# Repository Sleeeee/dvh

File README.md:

# dvh
Damn Vulnerable Hardware (DVH)

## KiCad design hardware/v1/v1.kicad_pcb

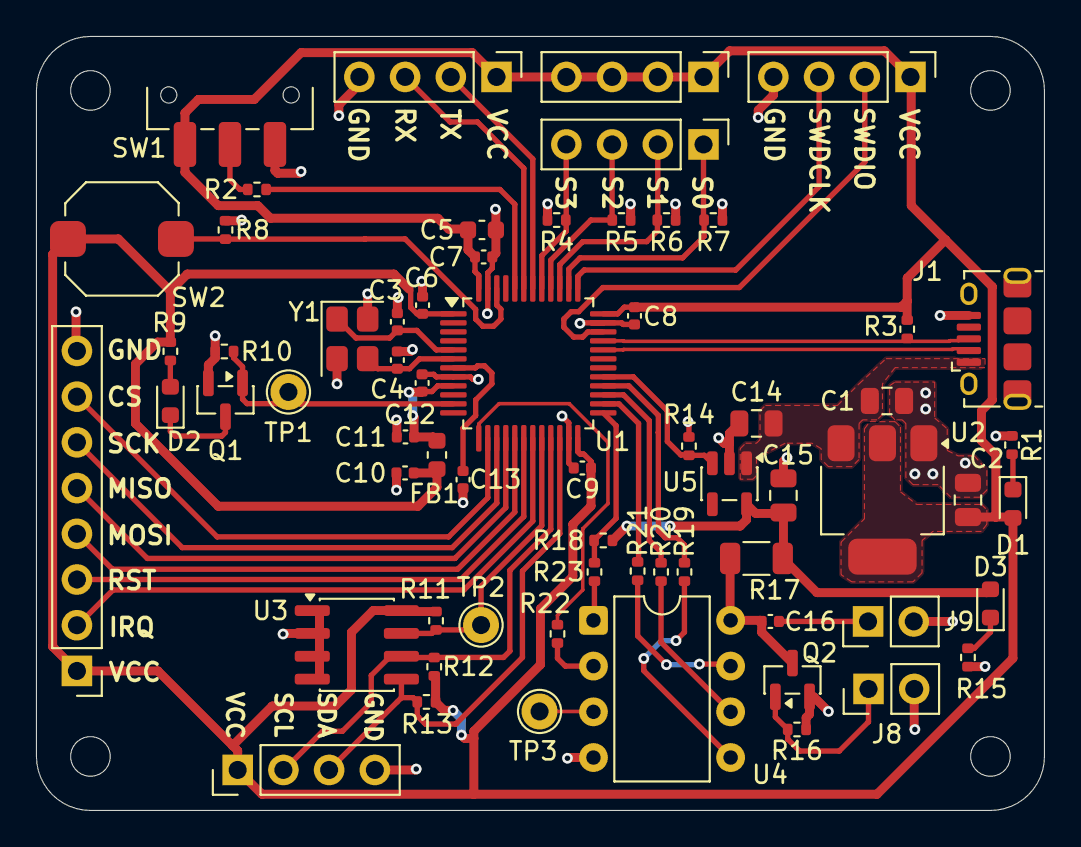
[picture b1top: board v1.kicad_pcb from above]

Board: 2 copper layers, 56.0 x 43.0 mm, 69 parts (0 on the bottom side), 50 nets.

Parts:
C1, C2: 22u; C_0805_2012Metric
C3, C4: 10p; C_0402_1005Metric
C5: 10u; C_0603_1608Metric
C6, C7, C8, C9, C13, C16: 100n; C_0402_1005Metric
C10, C11: 1u; C_0402_1005Metric
C12: 10n; C_0402_1005Metric
C14, C15: 1u; C_0805_2012Metric
D1, D3: RED; LED_0603_1608Metric
D2: GREEN; LED_0603_1608Metric
FB1: 120R; L_0603_1608Metric
H1, H2, H3, H4: MountingHole; MountingHole_2.2mm_M2
J1: USB_B_Micro; USB_Micro-B_Amphenol_10118194-0001LF_Horizontal
J2: SEL_IN; PinHeader_1x04_P2.54mm_Vertical
J3: SEL_VDD; PinHeader_1x04_P2.54mm_Vertical
J4: SWD_INT; PinHeader_1x04_P2.54mm_Vertical
J5: UART_INT; PinHeader_1x04_P2.54mm_Vertical
J6: I2C_INT; PinHeader_1x04_P2.54mm_Vertical
J7: RFID_INT; PinHeader_1x08_P2.54mm_Vertical
J8: GLITCH_IN; PinHeader_1x02_P2.54mm_Vertical
J9: GLITCH_EN; PinHeader_1x02_P2.54mm_Vertical
Q1, Q2: 2N7002; SOT-23
R1, R3, R9, R12, R13, R15, R19, R20, R21, R22, R23: 1k5; R_0402_1005Metric
R2, R4, R5, R6, R7, R8, R10, R11, R14, R16, R18: 10k; R_0402_1005Metric
R17: 47; R_1206_3216Metric
SW1: SW_BOOT0; SW_SPDT_CK_JS102011SAQN
SW2: LAB_RST; SW_Push_1TS009xxxx-xxxx-xxxx_6x6x5mm
TP1: DOOR; TestPoint_THTPad_D2.0mm_Drill1.0mm
TP2: WP; TestPoint_THTPad_D2.0mm_Drill1.0mm
TP3: GLITCH_TRIG; TestPoint_THTPad_D2.0mm_Drill1.0mm
U1: STM32F103C8Tx; LQFP-48_7x7mm_P0.5mm
U2: AMS1117-3.3; SOT-223-3_TabPin2
U3: M24C02-WMN; SOIC-8_3.9x4.9mm_P1.27mm
U4: ATtiny85-20P; DIP-8_W7.62mm
U5: AP2112K-3.3; SOT-23-5
Y1: 16MHz; Crystal_SMD_3225-4Pin_3.2x2.5mm

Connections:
+3.3V: C2.1, C5.1, C6.1, C7.1, C8.1, C9.1, C10.1, D1.2 (A), FB1.1, J3.1, J3.2, J3.3, J3.4, J4.1, J5.1, J6.1, J7.1, R3.1, R9.2, R11.1, R12.1, R13.1, SW1.3 (C), SW2.1, U1.1 (VBAT), U1.24 (VDD), U1.36 (VDD), U1.48 (VDD), U2.2 (VO), U3.8 (VCC)
+3.3VA: C11.1, C12.1, FB1.2, U1.9 (VDDA)
+3.3V_ATTINY: C15.1, D3.2 (A), R17.1, R18.2, U5.5 (VOUT)
/Base/PWR_LED_K: D1.1 (K), R1.1
/Base/SW_BOOT0: R2.1, SW1.2 (B)
/Connectivity/DOOR_LED_A: D2.2 (A), R9.1
/Connectivity/DOOR_LED_K: D2.1 (K), Q1.3 (D)
/Glitching/ATTINY_MISO: R20.1, U4.6 (PB1)
/Glitching/ATTINY_MOSI: R19.1, U4.5 (AREF/PB0)
/Glitching/ATTINY_RST: R23.1, U4.1 (~RESET/PB5)
/Glitching/ATTINY_SCK: R21.1, U4.7 (PB2)
/Glitching/ATTINY_TRIG: TP3.1, U4.3 (XTAL2/PB4)
/Glitching/ATTINY_TX: R22.1, U4.2 (XTAL1/PB3)
/Glitching/ATTINY_VCC: C16.2, Q2.3 (D), R17.2, U4.8 (VCC)
/Glitching/GLITCH_EN: C16.1, J9.1
/Glitching/GLITCH_IN: J8.1, Q2.1 (G), R16.2
/Glitching/PWR_LED_K: D3.1 (K), R15.1
BOOT0: R2.2, U1.44 (BOOT0)
DOOR_OUT: Q1.1 (G), R10.2, TP1.1, U1.11 (PA1)
EEPROM_WP: R11.2, TP2.1, U1.20 (PB2), U3.7 (~WC)
GLITCH_RST_OUT: R18.1, R23.2, U1.25 (PB12)
GND: C1.2, C2.2, C3.2, C4.2, C5.2, C6.2, C7.2, C8.2, C9.2, C10.2, C11.2, C12.2, C13.2, C14.2, C15.2, J1.5 (GND), J4.4, J5.4, J6.4, J7.8, J8.2, J9.2, Q1.2 (S), Q2.2 (S), R1.2, R4.2, R5.2, R6.2, R7.2, R8.2, R10.1, R14.1, R15.2, R16.1, SW1.1 (A), U1.8 (VSSA), U1.23 (VSS), U1.35 (VSS), U1.47 (VSS), U2.1 (GND), U3.1 (E0), U3.2 (E1), U3.3 (E2), U3.4 (VSS), U4.4 (GND), U5.2 (GND), Y1.2 (G), Y1.4 (G)
HSE_IN: C3.1, U1.5 (PD0), Y1.1
HSE_OUT: C4.1, U1.6 (PD1), Y1.3
I2C_SCL: J6.2, R12.2, U1.21 (PB10), U3.6 (SCL)
I2C_SDA: J6.3, R13.2, U1.22 (PB11), U3.5 (SDA)
LAB_RST: R8.1, SW2.2, U1.46 (PB9)
LAB_S0: J2.1, R7.1, U1.38 (PA15)
LAB_S1: J2.2, R6.1, U1.39 (PB3)
LAB_S2: J2.3, R5.1, U1.40 (PB4)
LAB_S3: J2.4, R4.1, U1.41 (PB5)
LDO_EN: R14.2, U1.29 (PA8), U5.3 (EN)
NRST: C13.1, U1.7 (NRST)
RFID_IRQ: J7.2, U1.19 (PB1)
RFID_RST: J7.3, U1.18 (PB0)
SPI1_CS: J7.7, U1.14 (PA4)
SPI1_MISO: J7.5, U1.16 (PA6)
SPI1_MOSI: J7.4, U1.17 (PA7)
SPI1_SCK: J7.6, U1.15 (PA5)
SPI2_MISO: R20.2, U1.27 (PB14)
SPI2_MOSI: R19.2, U1.28 (PB15)
SPI2_SCK: R21.2, U1.26 (PB13)
SWDCLK: J4.3, U1.37 (PA14)
SWDIO: J4.2, U1.34 (PA13)
UART1_RX: J5.3, U1.43 (PB7)
UART1_TX: J5.2, U1.42 (PB6)
UART2_RX: R22.2, U1.13 (PA3)
USB_D+: J1.3 (D+), R3.2, U1.33 (PA12)
USB_D-: J1.2 (D-), U1.32 (PA11)
VBUS: C1.1, C14.1, J1.1 (VBUS), U2.3 (VI), U5.1 (VIN)

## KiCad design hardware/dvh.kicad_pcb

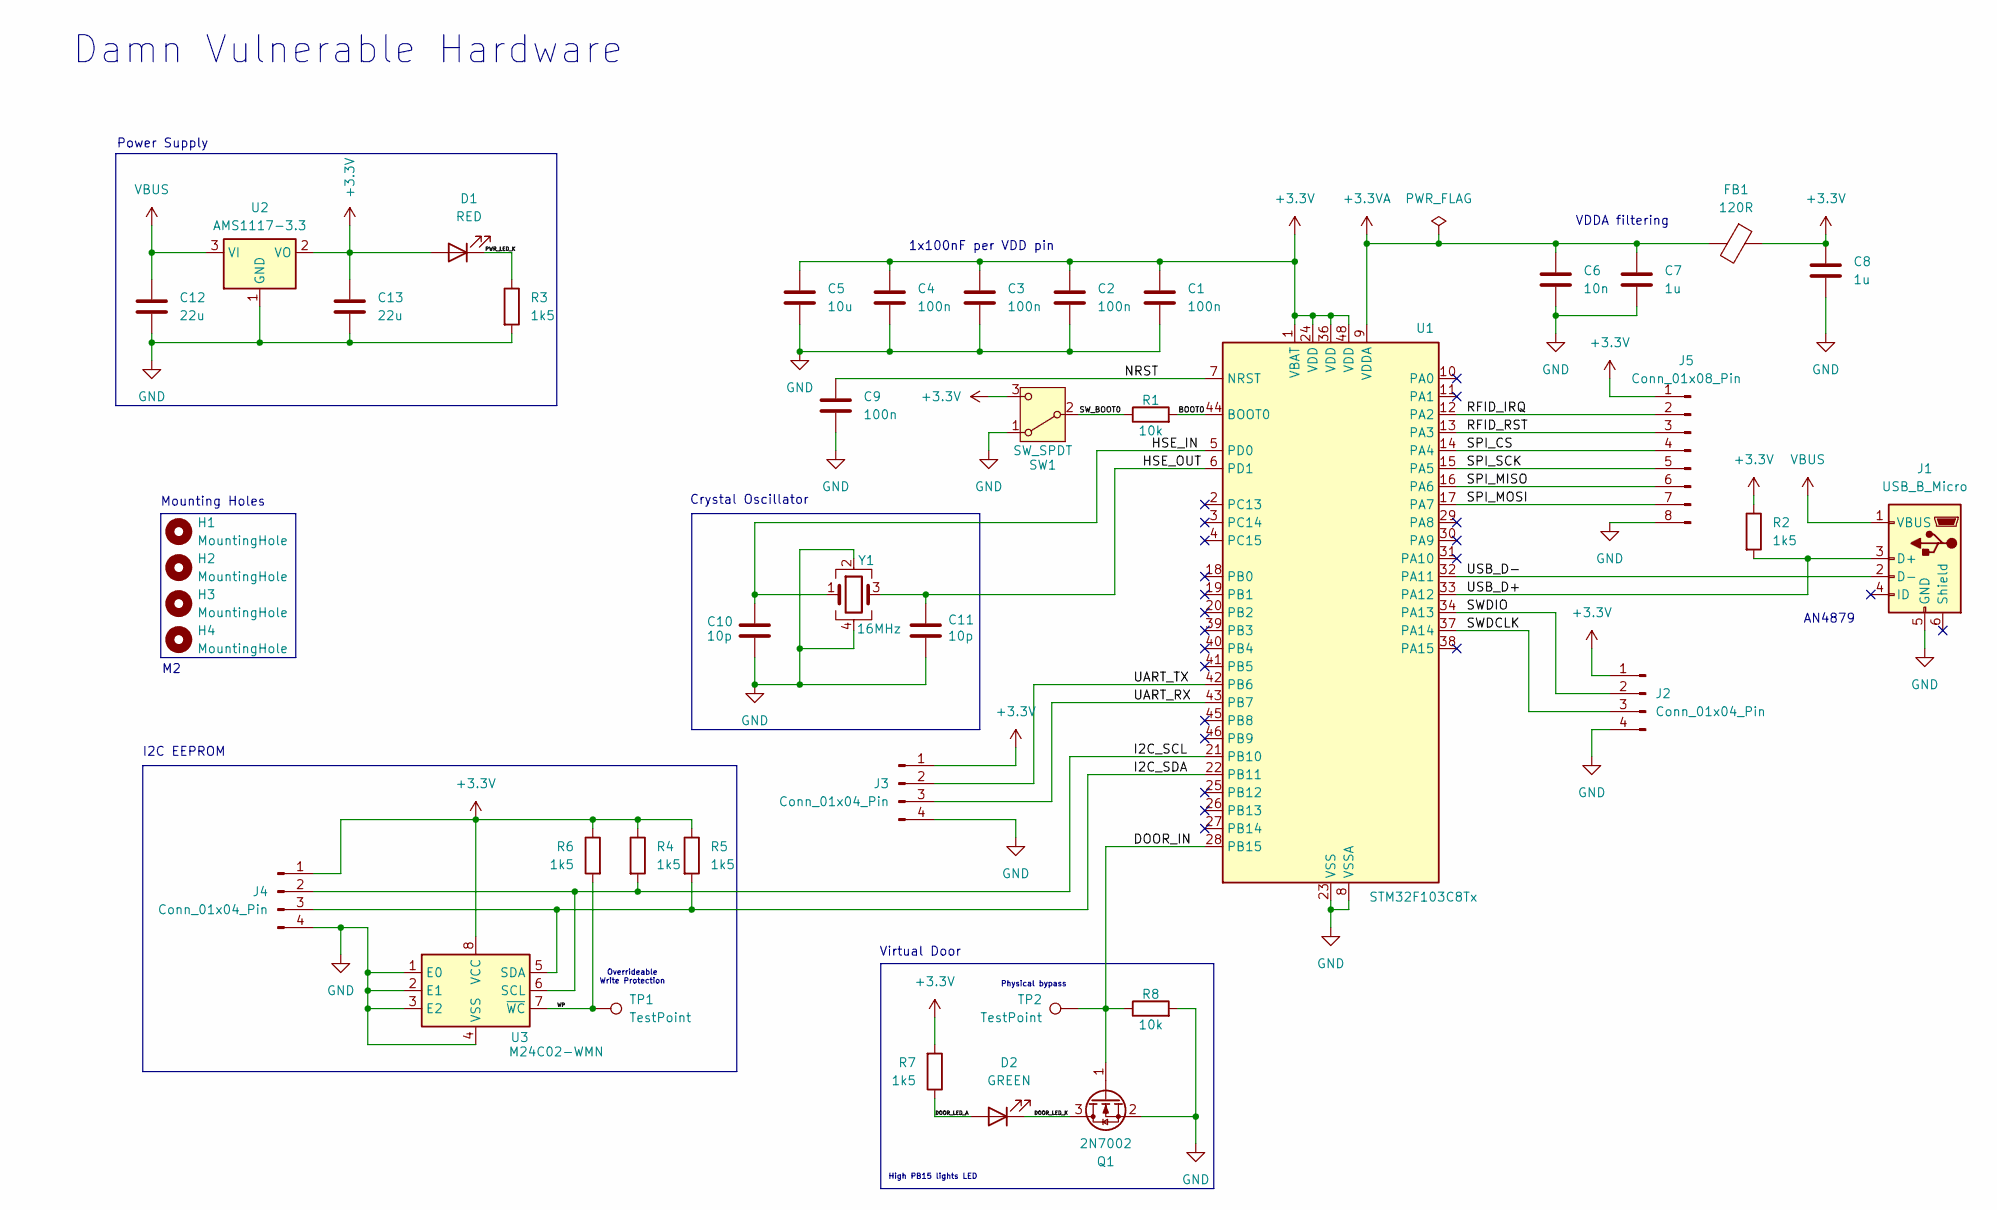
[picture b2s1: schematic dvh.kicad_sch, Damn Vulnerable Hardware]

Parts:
C1, C2, C3, C4, C9: 100n; C_0402_1005Metric
C5: 10u; C_0603_1608Metric
C6: 10n; C_0402_1005Metric
C7, C8: 1u; C_0402_1005Metric
C10, C11: 10p; C_0402_1005Metric
C12, C13: 22u; C_0805_2012Metric
D1: RED; LED_0603_1608Metric
D2: GREEN; LED_0603_1608Metric
FB1: 120R; L_0603_1608Metric
H1, H2, H3, H4: MountingHole; MountingHole_2.2mm_M2
J1: USB_B_Micro; USB_Micro-B_Amphenol_10118194-0001LF_Horizontal
J2, J3, J4: Conn_01x04_Pin; PinHeader_1x04_P2.54mm_Vertical
J5: Conn_01x08_Pin; PinHeader_1x08_P2.54mm_Vertical
Q1: 2N7002; SOT-23
R1, R8: 10k; R_0402_1005Metric
R2, R3, R4, R5, R6, R7: 1k5; R_0402_1005Metric
SW1: SW_SPDT; SW_SPDT_CK_JS102011SAQN
TP1, TP2: TestPoint; PinSocket_1x01_P2.54mm_Vertical
U1: STM32F103C8Tx; LQFP-48_7x7mm_P0.5mm
U2: AMS1117-3.3; SOT-223-3_TabPin2
U3: M24C02-WMN; SOIC-8_3.9x4.9mm_P1.27mm
Y1: 16MHz; Crystal_SMD_3225-4Pin_3.2x2.5mm

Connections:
+3.3V: C1.1, C2.1, C3.1, C4.1, C5.1, C8.1, C13.1, D1.2 (A), FB1.1, J2.1, J3.1, J4.1, J5.1, R2.1, R4.1, R5.1, R6.1, R7.2, SW1.3 (C), U1.1 (VBAT), U1.24 (VDD), U1.36 (VDD), U1.48 (VDD), U2.2 (VO), U3.8 (VCC); also elsewhere on the board
+3.3VA: C6.1, C7.1, FB1.2, U1.9 (VDDA)
/BOOT0: R1.2, U1.44 (BOOT0)
/DOOR_IN: Q1.1 (G), R8.1, TP2.1, U1.28 (PB15)
/DOOR_LED_A: D2.2 (A), R7.1
/DOOR_LED_K: D2.1 (K), Q1.3 (D)
/HSE_IN: C10.1, U1.5 (PD0), Y1.1
/HSE_OUT: C11.1, U1.6 (PD1), Y1.3
/I2C_SCL: J4.2, R4.2, U1.21 (PB10), U3.6 (SCL)
/I2C_SDA: J4.3, R5.2, U1.22 (PB11), U3.5 (SDA)
/NRST: C9.1, U1.7 (NRST)
/PWR_LED_K: D1.1 (K), R3.1
/RFID_IRQ: J5.2, U1.12 (PA2)
/RFID_RST: J5.3, U1.13 (PA3)
/SPI_CS: J5.4, U1.14 (PA4)
/SPI_MISO: J5.6, U1.16 (PA6)
/SPI_MOSI: J5.7, U1.17 (PA7)
/SPI_SCK: J5.5, U1.15 (PA5)
/SWDCLK: J2.3, U1.37 (PA14)
/SWDIO: J2.2, U1.34 (PA13)
/SW_BOOT0: R1.1, SW1.2 (B); also elsewhere on the board
/UART_RX: J3.3, U1.43 (PB7)
/UART_TX: J3.2, U1.42 (PB6)
/USB_D+: J1.3 (D+), R2.2, U1.33 (PA12)
/USB_D-: J1.2 (D-), U1.32 (PA11)
/WP: R6.2, TP1.1, U3.7 (~WC)
GND: C1.2, C2.2, C3.2, C4.2, C5.2, C6.2, C7.2, C8.2, C9.2, C10.2, C11.2, C12.2, C13.2, J1.5 (GND), J2.4, J3.4, J4.4, J5.8, Q1.2 (S), R3.2, R8.2, SW1.1 (A), U1.8 (VSSA), U1.23 (VSS), U1.35 (VSS), U1.47 (VSS), U2.1 (GND), U3.1 (E0), U3.2 (E1), U3.3 (E2), U3.4 (VSS), Y1.2, Y1.4; also elsewhere on the board
VBUS: C12.1, J1.1 (VBUS), U2.3 (VI)

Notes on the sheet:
Overrideable Write Protection
Power Supply
Mounting Holes
Physical bypass
VDDA filtering
High PB15 lights LED
Crystal Oscillator
Damn Vulnerable Hardware
Virtual Door
I2C EEPROM
AN4879
1x100nF per VDD pin

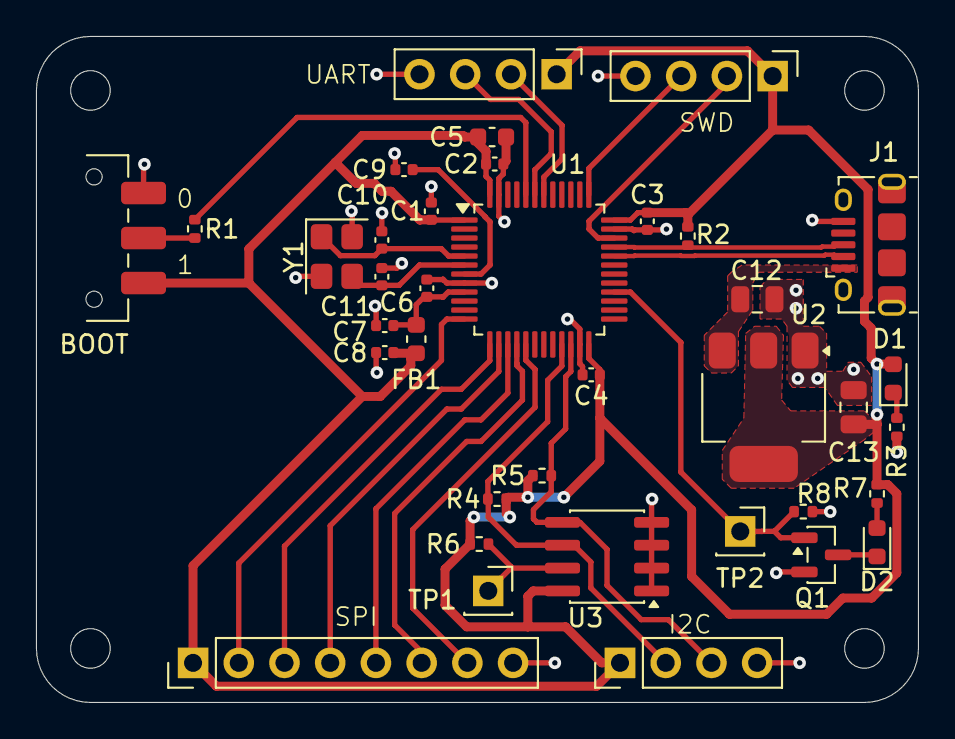
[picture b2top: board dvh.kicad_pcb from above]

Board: 2 copper layers, 49.0 x 37.0 mm, 41 parts (0 on the bottom side), 28 nets.

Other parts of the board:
BOOT: SW_SPDT; SW_SPDT_CK_JS102011SAQN

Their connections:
+3.3V: BOOT.3 (C); also elsewhere on the board
/SW_BOOT0: BOOT.2 (B); also elsewhere on the board
GND: BOOT.1 (A); also elsewhere on the board

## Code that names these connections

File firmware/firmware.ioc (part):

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Mcu.Name=STM32F103C(8-B)Tx
Mcu.Package=LQFP48
Mcu.UserName=STM32F103C8Tx
PA1.GPIOParameters=GPIO_Label
PA1.GPIO_Label=DOOR_OUT
PA1.Signal=GPIO_Output
PA11.Mode=Device
PA11.Signal=USB_DM
PA12.Mode=Device
PA12.Signal=USB_DP
PA13.GPIOParameters=GPIO_Label
PA13.GPIO_Label=SWDIO
PA13.Mode=Serial_Wire
PA13.Signal=SYS_JTMS-SWDIO
PA14.GPIOParameters=GPIO_Label
PA14.GPIO_Label=SWDCLK
PA14.Mode=Serial_Wire
PA14.Signal=SYS_JTCK-SWCLK
PA15.GPIOParameters=GPIO_Label
PA15.GPIO_Label=LAB_S0
PA15.Signal=GPIO_Input
PA2.Mode=Asynchronous
PA2.Signal=USART2_TX
PA3.Mode=Asynchronous
PA3.Signal=USART2_RX
PA4.GPIOParameters=GPIO_Label
PA4.GPIO_Label=SCREEN_BLK
PA4.Signal=GPIO_Output
PA5.GPIOParameters=GPIO_Label
PA5.GPIO_Label=SPI1_SCK
PA5.Mode=TX_Only_Simplex_Unidirect_Master
PA5.Signal=SPI1_SCK
PA7.GPIOParameters=GPIO_Label
PA7.GPIO_Label=SPI1_MOSI
PA7.Mode=TX_Only_Simplex_Unidirect_Master
PA7.Signal=SPI1_MOSI
PA8.GPIOParameters=GPIO_Label
PA8.GPIO_Label=LDO_EN
PA8.Signal=GPIO_Output
PB0.GPIOParameters=GPIO_Label
PB0.GPIO_Label=SCREEN_RES
PB0.Signal=GPIO_Output
PB1.GPIOParameters=GPIO_Label
PB1.GPIO_Label=SCREEN_DC
PB1.Signal=GPIO_Output
PB10.GPIOParameters=GPIO_Label
PB10.GPIO_Label=I2C_SCL
PB10.Mode=I2C
PB10.Signal=I2C2_SCL
PB11.GPIOParameters=GPIO_Label
PB11.GPIO_Label=I2C_SDA
PB11.Mode=I2C
PB11.Signal=I2C2_SDA
PB12.GPIOParameters=GPIO_Label
PB12.GPIO_Label=ATTINY_RST
PB12.Signal=GPIO_Output
PB13.Mode=Full_Duplex_Master
PB13.Signal=SPI2_SCK
PB14.Mode=Full_Duplex_Master
PB14.Signal=SPI2_MISO
PB15.Mode=Full_Duplex_Master
PB15.Signal=SPI2_MOSI
PB2.GPIOParameters=GPIO_PuPd,GPIO_Label,GPIO_ModeDefaultOutputPP
PB2.GPIO_Label=EEPROM_WP
PB2.GPIO_ModeDefaultOutputPP=GPIO_MODE_OUTPUT_OD
PB2.GPIO_PuPd=GPIO_NOPULL
PB2.Signal=GPIO_Output
PB3.GPIOParameters=GPIO_Label
PB3.GPIO_Label=LAB_S1
PB3.Signal=GPIO_Input
PB4.GPIOParameters=GPIO_Label
PB4.GPIO_Label=LAB_S2
PB4.Signal=GPIO_Input
PB5.GPIOParameters=GPIO_Label
PB5.GPIO_Label=LAB_S3
PB5.Signal=GPIO_Input
PB6.GPIOParameters=GPIO_Label
PB6.GPIO_Label=UART_TX
PB6.Mode=Asynchronous
PB6.Signal=USART1_TX
PB7.GPIOParameters=GPIO_Label
PB7.GPIO_Label=UART_RX
PB7.Mode=Asynchronous
PB7.Signal=USART1_RX
PB9.GPIOParameters=GPIO_Label
PB9.GPIO_Label=LAB_RST
PB9.Signal=GPIO_Input
PD0-OSC_IN.GPIOParameters=GPIO_Label
PD0-OSC_IN.GPIO_Label=HSE_IN
PD0-OSC_IN.Mode=HSE-External-Oscillator
PD0-OSC_IN.Signal=RCC_OSC_IN
PD1-OSC_OUT.GPIOParameters=GPIO_Label
PD1-OSC_OUT.GPIO_Label=HSE_OUT
PD1-OSC_OUT.Mode=HSE-External-Oscillator
PD1-OSC_OUT.Signal=RCC_OSC_OUT
RCC.HSEDivPLL=RCC_HSE_PREDIV_DIV2
RCC.HSE_VALUE=16000000
RCC.SYSCLKFreq_VALUE=72000000
RCC.SYSCLKSource=RCC_SYSCLKSOURCE_PLLCLK
board=custom

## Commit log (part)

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2025-11-17 DVH #1 Set up basic project structure and toolchain
2025-11-17 DVH #1 Add documentation for development environment setup
2025-11-17 DVH #3 Add firmware with flag for easy dumping
2025-11-27 DVH #6 Publish version 0.1 schematics
2025-12-23 DVH #1 Remove the deprecated Pico toolchain
2025-12-23 DVH #6 Rename the pcb/ directory to hardware/ for improved consistency
2025-12-23 DVH #9 Implement STM32 CMake toolchain (raw STM32CubeMX output)
2025-12-23 DVH #9 Add test code to blink LED
2025-12-25 DVH #9 Configure OpenOCD, automate .bin building and flashing command execution
2025-12-25 DVH #1 Remove deprecated development documentation
2025-12-25 DVH #9 Add complete documentation for setting up the Debugprobe and flashing the DVH board
2025-12-25 DVH #9 Add pictures to debugprobe and flash docs
2025-12-26 DVH #9 Add complete documentation for setting up the toolchain
2025-12-26 DVH #2 Plant hidden plaintext flag readable from firmware dumping
2025-12-28 DVH #2 Plant encrypted flags and decryption logic
2025-12-28 DVH #2 Add README.md for SWD lab
2025-12-30 DVH #2 Add instructions and complete walkthrough for SWD lab
2025-12-30 DVH #2 #4 #9 Fix inacurrate image blur, center and resize images
2026-01-09 DVH #9 Update toolchain documentation with latest build command
2026-01-09 DVH #17 Add auto-release workflow
2026-01-14 DVH #18 Import Unity testing library files
2026-01-14 DVH #2 Remove unnecessary main.h import
2026-01-14 DVH #2 Add unit tests
2026-01-19 DVH #18 Add bash script for automating unit test execution
2026-01-19 DVH #18 Add GitHub Actions workflow for running unit tests on main push
2026-01-19 DVH #18 Add initial Renode platform description
2026-01-19 DVH #18 Enforce stricter (unique) naming convention and move flags to global scope to allow ELF symbol reading for Renode
2026-01-19 DVH #18 Prevent inline optimization to ensure the Solve_Flag functions appear in the symbols table
2026-01-19 DVH #18 Ignore Renode output files
2026-01-19 DVH #2 Add SWD lab Renode testing
2026-01-19 DVH #18 Add Renode testing automation script
2026-01-19 DVH #18 Update testing workflow to run Renode tests
2026-01-20 DVH #18 Implement new simulation build option for Renode
2026-01-20 DVH #18 Fix Renode testing code passing but not actually performing the tests
2026-01-20 DVH #18 Add testing documentation
2026-01-20 DVH #15 Implement lab selection based on GPIO inputs on firmware boot
2026-01-21 DVH #15 Add lab select blinking feedback
2026-01-21 DVH #15 Move ilab.h into a more appropriate public folder
2026-01-21 DVH #15 Implement HAL mocks to adapt unit tests to improved lab structure
2026-01-21 DVH #15 Add unit testing for lab selection, some refactoring
2026-01-21 DVH #11 Implement UART file structure, write hello world
2026-01-22 DVH #11 Implement shared flag decryption helper
2026-01-22 DVH #11 Implement basic UART shell behavior
2026-01-23 DVH #11 Refactor and publish multi-access shell behavior
2026-01-26 DVH #11 Implement mock boot sequence, small shell adjustments
2026-01-26 DVH #11 Implement user database dumping and root password checking, refactor utils_flag to utils_secrets
2026-01-27 DVH #11 Add testing for secrets utility functions
2026-01-28 DVH #11 Refactor UART and shell helpers (mostly hardware decoupling), write unit tests for helpers and UART lab commands
2026-01-30 DVH #11 Tell user to ask for help in UART shell
2026-01-30 DVH #18 Improve Robot script code format
2026-01-30 DVH #11 Implement Renode testing
2026-01-31 DVH #11 Add README, instructions and complete walkthrough for UART lab
2026-02-21 DVH #11 Add README, instructions and walkthrough for UART
2026-02-21 DVH #14 Improve internal lab structure to allow resetting, write boilerplate for I2C lab
2026-03-06 DVH #14 Small file structure refactoring
2026-03-07 DVH #14 Implement lab reset sequence, small file structure refactoring
2026-03-20 DVH #14 Implement M24C02-W I2C driver
2026-03-20 DVH #14 Add lab reset error status, implement I2C lab reset
2026-03-21 DVH #21 Add snippet language indications and center tables
2026-03-21 DVH #14 Refactor shell, UART and secrets helpers for better lab separation of concerns
2026-03-21 DVH #14 Refactor lab init to return status
2026-03-21 DVH #14 Implement I2C lab design
2026-03-22 DVH #21 Small documentation changes
2026-03-29 DVH #14 Refactor unit tests to match updated sources
2026-04-04 DVH #14 Add mocks for I2C unit testing, refactor general structure
2026-04-06 DVH #14 Add full comprehensive documentation for I2C lab
2026-04-12 DVH #24 Implement unit testing for I2C lab, refactor mock architecture, fix tiny typo
2026-04-12 DVH #24 Add skeleton for Renode testing, not implemented yet (Renode I2C driver issues)
2026-05-03 DVH #19 Add Kicad project, schematic and board files
2026-05-03 DVH #22 Migrate firmware to match v1 hardware architecture (regenerate from CubeMX, add software EEPROM WP control, change pin names, remove v0 workarounds)
2026-05-03 DVH #22 Adapt mock GPIO definitions to v1 board
2026-05-03 DVH #22 Migrade Renode tests to pcb v1
2026-05-03 DVH #25 Update CubeMX configuration (migrate SPI interface for ST7789 compatibility)
2026-05-18 DVH #25 Integrate ST7789 screen to the project, add bootstrap feedback
2026-05-19 DVH #25 Add screen helpers for consistent screen text display
2026-05-19 DVH #25 Implement screen feedback on SWD lab
2026-05-19 DVH #25 #22 Fix critical CubeMX configuration (stabilizes ST7789 display)
2026-05-19 DVH #25 Implement screen feedback on UART lab
2026-05-19 DVH #25 Implement screen feedback on I2C lab
2026-05-19 DVH #25 Add unit tests for ST7789 integration (utils and labs), improve mocks
2026-05-20 DVH #13 Improve toolchain to allow automatic building of the ATTiny payload as a header file (attiny.h, gitignored)
2026-05-20 DVH #13 Configure ATTiny-facing SPI and UART to compatible speeds
2026-05-20 DVH #13 Add ISP driver and basic glitch lab structure, program ATTiny on lab reset, sanity check UART connectivity
2026-05-21 DVH #13 Implement glitchable loop as a lab PoC
2026-05-22 DVH #13 Increase glitching attack surface, plant flag one (on fast brownout) and flag two (on successful glitch)
2026-05-23 DVH #13 Add final adjustments to glitching UI/UX
2026-05-23 DVH #13 Refactor lab, decouple logic for cleaner testing
2026-05-23 DVH #13 Implement glitch lab unit tests, refactor part of the helper mocks for compatibility
2026-05-24 DVH #13 Add Renode tests for glitch lab, some Renode refactoring
2026-05-24 DVH #14 Fix missing text in I2C instructions document
2026-05-24 DVH #13 Add voltage glitching lab documentation and assets (ATTiny firmware and Glitcher script)
2026-05-24 Fix regression in building/testing pipeline
2026-05-27 DVH #30 Pin workflow actions to verified SHA
2026-05-27 DVH #30 Add basic dependabot config
2026-05-27 DVH #26 Add OpenSCAD model (first PCB case attempt)
2026-05-27 DVH #31 Add Kibot configuration, add Gerber release pipeline job
2026-05-29 Add unit test code coverage
2026-06-04 Bump actions/checkout from 6.0.2 to 6.0.3
    Bumps [actions/checkout](https://github.com/actions/checkout) from 6.0.2 to 6.0.3.
    - [Release notes](https://github.com/actions/checkout/releases)
    - [Changelog](https://github.com/actions/checkout/blob/main/CHANGELOG.md)
    - [Commits](https://github.com/actions/checkout/compare/de0fac2e4500dabe0009e67214ff5f5447ce83dd...df4cb1c069e1874edd31b4311f1884172cec0e10)
    ---
    updated-dependencies:
2026-06-24 Bump actions/checkout from 6.0.2 to 7.0.0
    Bumps [actions/checkout](https://github.com/actions/checkout) from 6.0.2 to 7.0.0.
    - [Release notes](https://github.com/actions/checkout/releases)
    - [Changelog](https://github.com/actions/checkout/blob/main/CHANGELOG.md)
    - [Commits](https://github.com/actions/checkout/compare/de0fac2e4500dabe0009e67214ff5f5447ce83dd...9c091bb21b7c1c1d1991bb908d89e4e9dddfe3e0)
    ---
    updated-dependencies:
2026-06-24 Bump softprops/action-gh-release from 3.0.0 to 3.0.1
    Bumps [softprops/action-gh-release](https://github.com/softprops/action-gh-release) from 3.0.0 to 3.0.1.
    - [Release notes](https://github.com/softprops/action-gh-release/releases)
    - [Changelog](https://github.com/softprops/action-gh-release/blob/master/CHANGELOG.md)
    - [Commits](https://github.com/softprops/action-gh-release/compare/b4309332981a82ec1c5618f44dd2e27cc8bfbfda...718ea10b132b3b2eba29c1007bb80653f286566b)
    ---
    updated-dependencies:
